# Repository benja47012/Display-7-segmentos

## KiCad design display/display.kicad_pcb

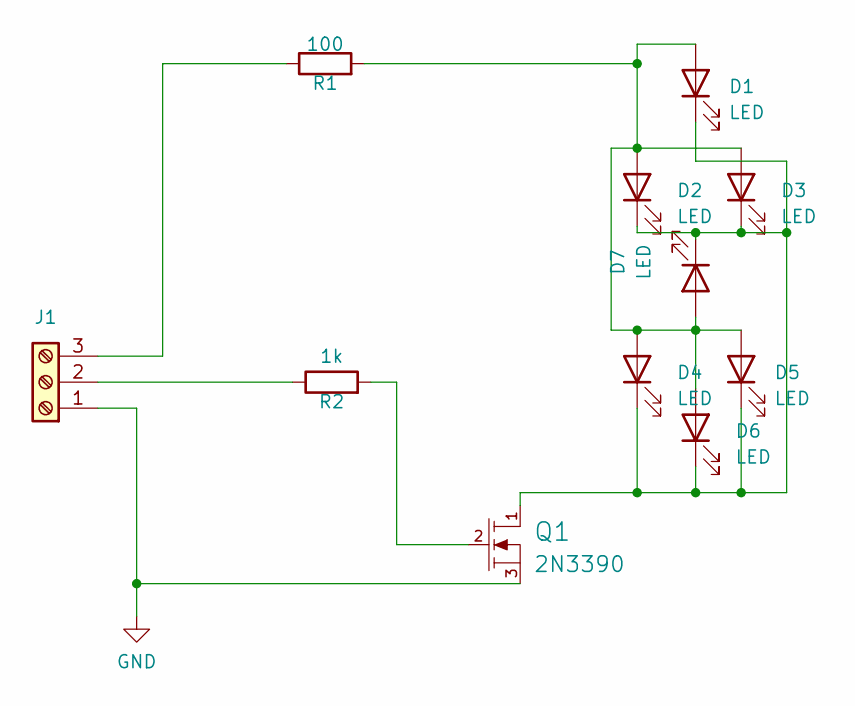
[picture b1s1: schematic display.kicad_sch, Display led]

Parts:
D1, D2, D3, D4, D5, D6, D7: LED; LED_D5.0mm
J1: Screw_Terminal_01x03; PinHeader_1x03_P2.54mm_Vertical
Q1: 2N3390; TO-92_Inline
R1: 100; R_Axial_DIN0207_L6.3mm_D2.5mm_P10.16mm_Horizontal
R2: 1k; R_Axial_DIN0207_L6.3mm_D2.5mm_P10.16mm_Horizontal

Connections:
GND: J1.1, Q1.3 (S)
unnamed: D1.2 (A), D2.2 (A), D3.2 (A), D4.2 (A), D5.2 (A), D6.2 (A), D7.2 (A), R1.2
unnamed: D1.1 (K), D2.1 (K), D3.1 (K), D4.1 (K), D5.1 (K), D6.1 (K), D7.1 (K), Q1.1 (D)
unnamed: J1.2, R2.1
unnamed: J1.3, R1.1
unnamed: Q1.2 (G), R2.2

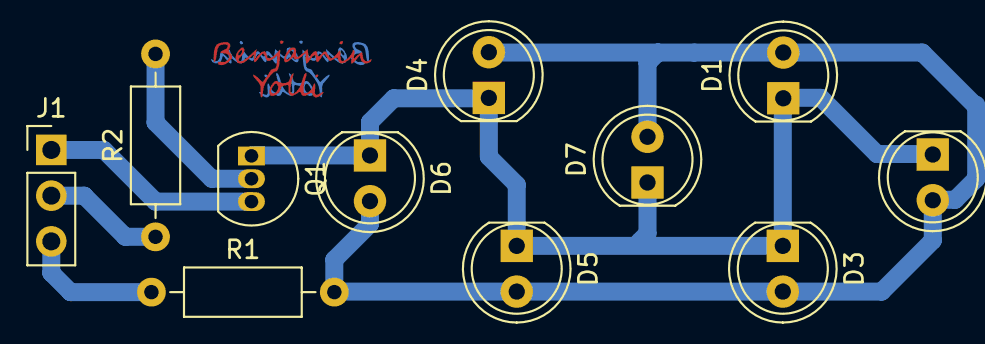
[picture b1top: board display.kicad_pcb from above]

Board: 2 copper layers, 11 parts (0 on the bottom side), 6 nets.

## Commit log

2023-11-03 Display-7-Segentos
2023-11-03 Display-led-7-segmentos-terminado
